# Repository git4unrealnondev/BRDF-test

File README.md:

# BRDF-test

маленькая картошка, работа в процессе. 
Сделайте много фотографий из света и дает нормальные и цветные изображения.
нет ответственности, если нет работы

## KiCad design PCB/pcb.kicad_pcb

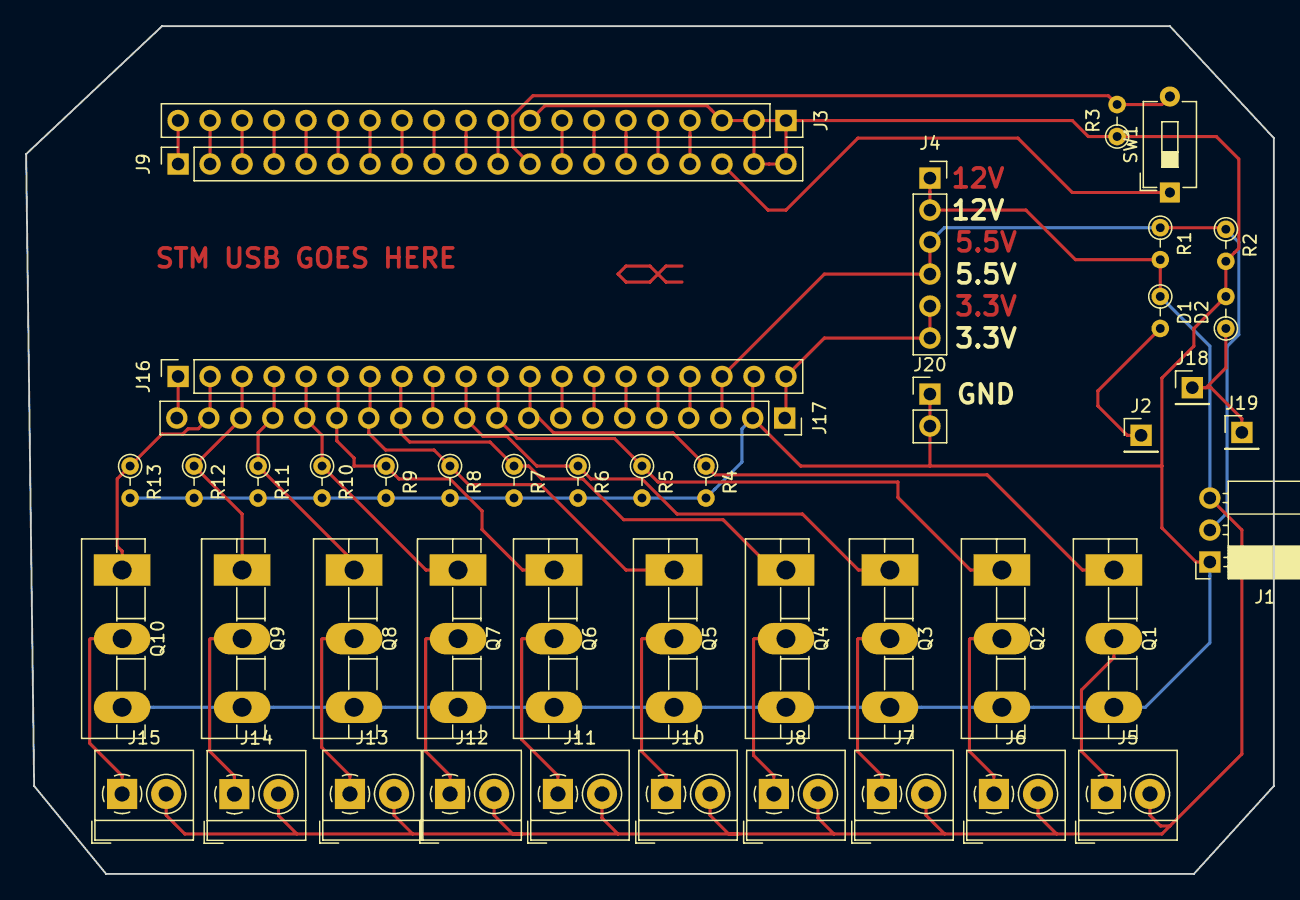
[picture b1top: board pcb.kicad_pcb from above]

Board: 2 copper layers, 99.1 x 67.3 mm, 46 parts (0 on the bottom side), 51 nets.

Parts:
D1, D2: D_ALT; R_Axial_DIN0204_L3.6mm_D1.6mm_P2.54mm_Vertical
J1: Conn_01x03_Female; PinSocket_1x03_P2.54mm_Horizontal
J2, J18, J19: Conn_01x01_Female; PinHeader_1x01_P2.54mm_Vertical
J3, J9, J16, J17: Conn_01x20_Female; PinSocket_1x20_P2.54mm_Vertical
J4: Conn_01x06_Female; PinSocket_1x06_P2.54mm_Vertical
J5, J6, J7, J8, J10, J11, J12, J13, J14, J15: Screw_Terminal_01x02; TerminalBlock_4Ucon_1x02_P3.50mm_Horizontal
J20: Conn_01x02_Female; PinHeader_1x02_P2.54mm_Vertical
Q1, Q2, Q3, Q4, Q5, Q6, Q7, Q8, Q9, Q10: QM6006D; TO-3PB-3_Vertical
R1: 22K; R_Axial_DIN0204_L3.6mm_D1.6mm_P2.54mm_Vertical
R2: 15K; R_Axial_DIN0204_L3.6mm_D1.6mm_P2.54mm_Vertical
R3, R4, R5, R6, R7, R8, R9, R10, R11, R12, R13: 10K; R_Axial_DIN0204_L3.6mm_D1.6mm_P2.54mm_Vertical
SW1: SW_Push; SW_DIP_SPSTx01_Slide_6.7x4.1mm_W7.62mm_P2.54mm_LowProfile

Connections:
/3.3V: J4.5, J4.6, J16.20, J17.1
/5V: J1.2, J4.3, J4.4, J16.18, J17.3, R1.1, R2.1
/GND: D2.2, J1.1, J3.1, J3.2, J3.3, J3.9, J9.19, J9.20, J16.19, J17.2, J20.1, J20.2, Q1.3, Q2.3, Q3.3, Q4.3, Q5.3, Q6.3, Q7.3, Q8.3, Q9.3, Q10.3, R2.2, R3.1, R4.2, R5.2, R6.2, R7.2, R8.2, R9.2, R10.2, R11.2, R12.2, R13.2
unnamed: D1.1, J1.3, J4.1, J4.2, J5.2, J6.2, J7.2, J8.2, J10.2, J11.2, J12.2, J13.2, J14.2, J15.2, R1.2
unnamed: D1.2, J2.1
unnamed: D2.1, J18.1, J19.1
unnamed: J3.4, J9.17
unnamed: J3.5, J9.16
unnamed: J3.6, J9.15
unnamed: J3.7, J9.14
unnamed: J3.8, J9.13
unnamed: J3.10, J9.11
unnamed: J3.11, J9.10
unnamed: J3.12, J9.9
unnamed: J3.13, J9.8
unnamed: J3.14, J9.7
unnamed: J3.15, J9.6
unnamed: J3.16, J9.5
unnamed: J3.17, J9.4
unnamed: J3.18, J9.3
unnamed: J3.19, J9.2
unnamed: J3.20, J9.1
unnamed: J5.1, Q1.2
unnamed: J6.1, Q2.2
unnamed: J7.1, Q3.2
unnamed: J8.1, Q4.2
unnamed: J9.12, R3.2, SW1.2
unnamed: J9.18, SW1.1
unnamed: J10.1, Q5.2
unnamed: J11.1, Q6.2
unnamed: J12.1, Q7.2
unnamed: J13.1, Q8.2
unnamed: J14.1, Q9.2
unnamed: J15.1, Q10.2
unnamed: J16.1, J17.20
unnamed: J16.2, J17.19, Q10.1, R13.1
unnamed: J16.3, J17.18, Q9.1, R12.1
unnamed: J16.4, J17.17, Q8.1, R11.1
unnamed: J16.5, J17.16, Q7.1, R10.1
unnamed: J16.6, J17.15, Q6.1, R9.1
unnamed: J16.7, J17.14, Q5.1, R8.1
unnamed: J16.8, J17.13, Q4.1, R7.1
unnamed: J16.9, J17.12
unnamed: J16.10, J17.11, Q3.1, R6.1
unnamed: J16.11, J17.10, Q2.1, R5.1
unnamed: J16.12, J17.9, Q1.1, R4.1
unnamed: J16.13, J17.8
unnamed: J16.14, J17.7
unnamed: J16.15, J17.6
unnamed: J16.16, J17.5
unnamed: J16.17, J17.4

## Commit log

2018-12-22 Update For Work Dir
2018-12-28 Updated Code
